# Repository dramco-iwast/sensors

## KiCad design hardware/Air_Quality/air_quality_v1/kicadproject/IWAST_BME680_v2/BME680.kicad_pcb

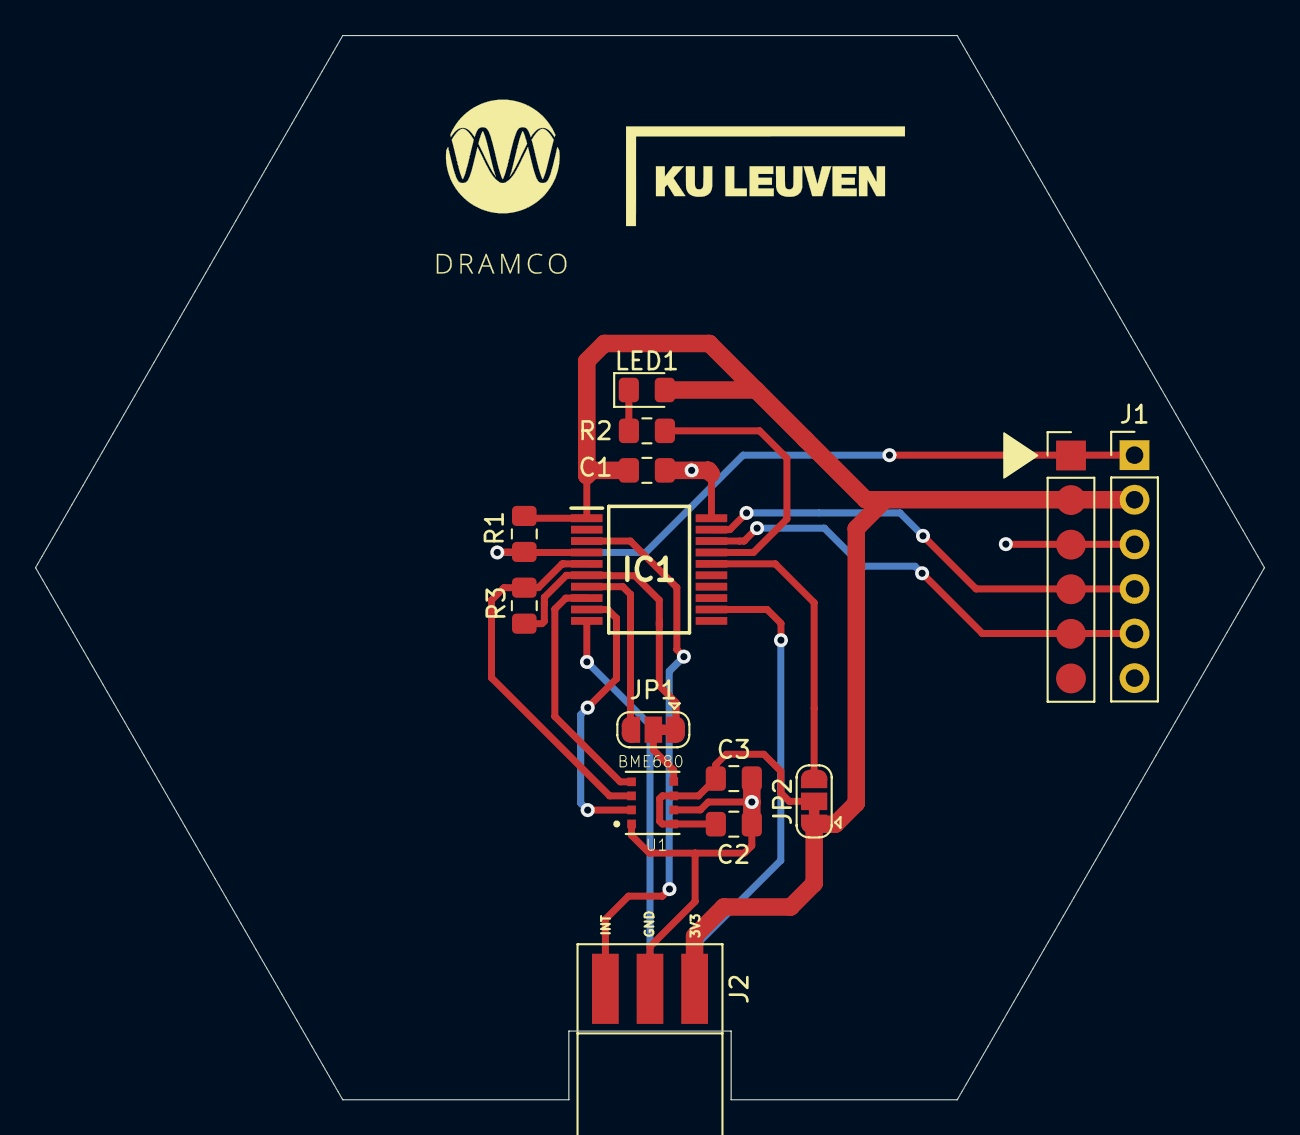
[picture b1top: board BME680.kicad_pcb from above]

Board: 2 copper layers, 70.0 x 60.6 mm, 13 parts (0 on the bottom side), 18 nets.

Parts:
C1, C2, C3: 100n; C_0805_2012Metric_Pad1.15x1.40mm_HandSolder
IC1: PIC16F18446-I_SS; SOP65P780X200-20N
J1: PICKit3; PinHeader_1x06_P2.54mm_Vertical
J2: MASTER; ConnectorHorizontalPcb
JP1: 3-wire; SolderJumper-3_P1.3mm_Bridged12_RoundedPad1.0x1.5mm
JP2: VDD Sensor; SolderJumper-3_P1.3mm_Bridged12_RoundedPad1.0x1.5mm
LED1: SML-D12Y1WT86; LED_0805_2012Metric_Pad1.15x1.40mm_HandSolder
R1, R3: 10k; R_0805_2012Metric_Pad1.15x1.40mm_HandSolder
R2: 1k; R_0805_2012Metric_Pad1.15x1.40mm_HandSolder
U1: BME680; PSON80P300X300X100-8N

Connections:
+3V3: C1.1, IC1.1, J1.2, J2.1, JP2.1, LED1.2, R1.1
/CS1: IC1.9, U1.2
/ICSPCLK: IC1.18, J1.5
/ICSPDAT: IC1.19, J1.4
/INT: IC1.3, J2.3
/MCLR: IC1.4, J1.1, R1.2
/MISO-SDI2: IC1.6, JP1.1, R3.2
/MOSI-SDO2: IC1.5, R3.1, U1.3
/NEWDATA: IC1.7, JP1.3
/SCK: IC1.8, U1.4
/SCL: IC1.10, J2.5
/SDA: IC1.12, J2.4
/USER_LED: IC1.17, R2.2
/VDD_sensor: IC1.16, JP2.3
GND: C1.2, C2.2, C3.2, IC1.20, J1.3, J2.2, U1.1, U1.7
unnamed: C2.1, C3.1, JP2.2, U1.6, U1.8
unnamed: JP1.2, U1.5
unnamed: LED1.1, R2.1

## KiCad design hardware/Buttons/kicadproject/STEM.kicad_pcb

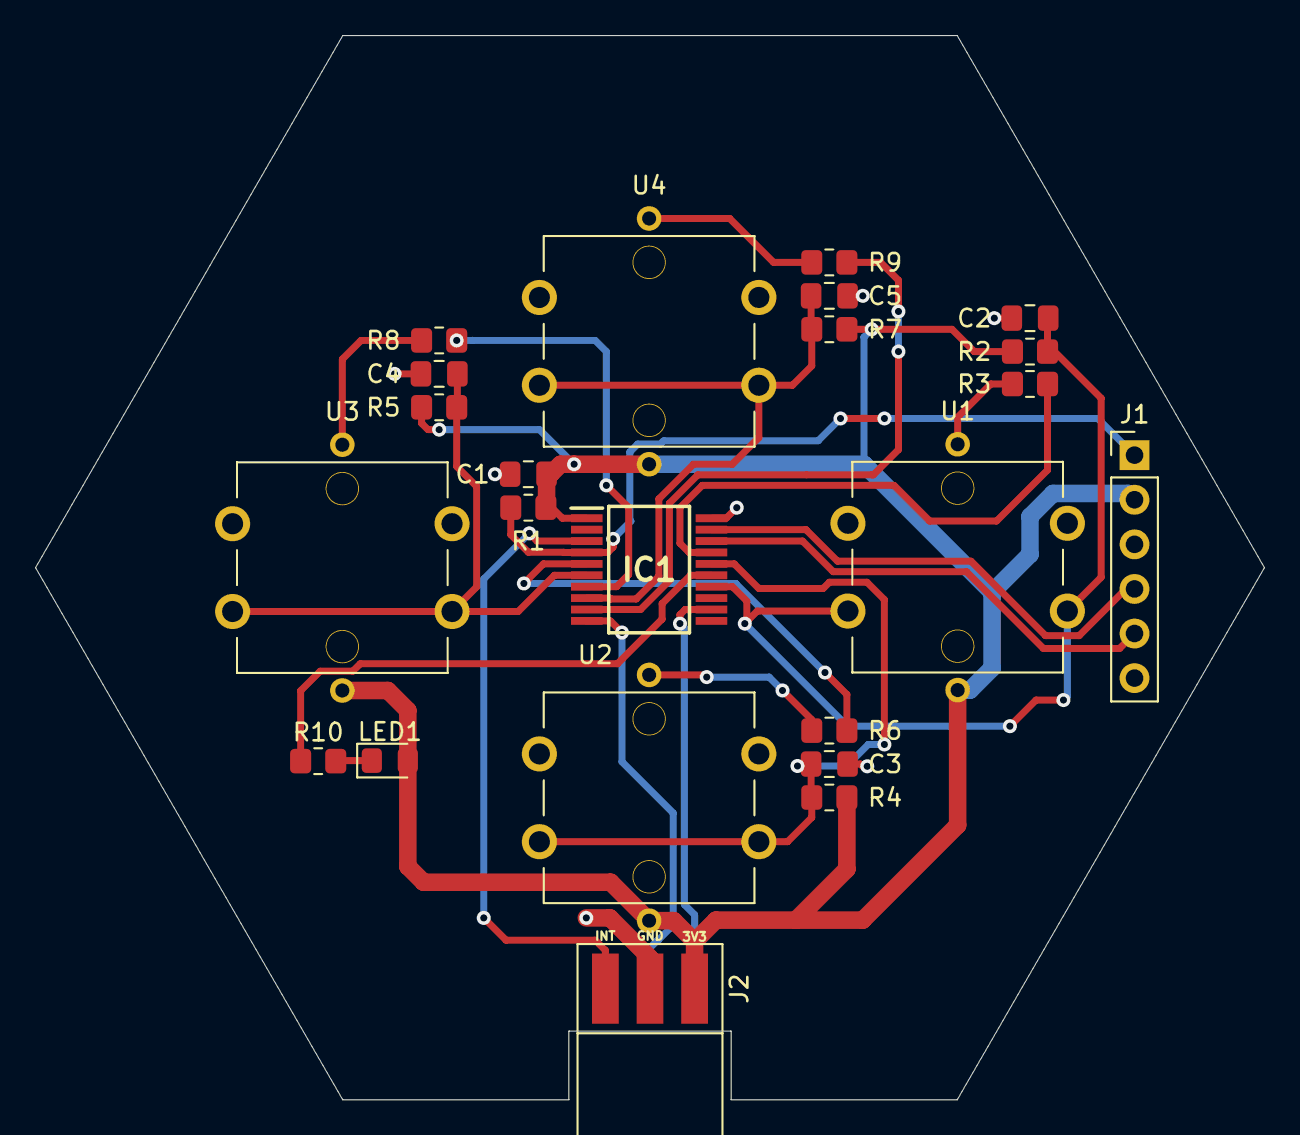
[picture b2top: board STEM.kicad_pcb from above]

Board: 2 copper layers, 70.0 x 60.6 mm, 23 parts (0 on the bottom side), 22 nets.

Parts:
C1, C2, C3, C4, C5: 100n; C_0805_2012Metric_Pad1.18x1.45mm_HandSolder
IC1: PIC16F18446-I_SS; SOP65P780X200-20N
J1: PICKit3; PinHeader_1x06_P2.54mm_Vertical
J2: MASTER; ConnectorHorizontalPcb
LED1: SML-D12Y1WT86; LED_0805_2012Metric_Pad1.15x1.40mm_HandSolder
R1: 10k; R_0805_2012Metric_Pad1.20x1.40mm_HandSolder
R2, R4, R5, R7: 100k; R_0805_2012Metric_Pad1.20x1.40mm_HandSolder
R3, R6, R8, R9, R10: 1k; R_0805_2012Metric_Pad1.20x1.40mm_HandSolder
U1, U2, U3, U4: button; aliButton

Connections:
+3V3: C1.1, IC1.1, J1.2, J2.1, LED1.2, R1.1, R2.1, R4.1, R5.1, R7.1, U1.5, U2.5, U3.5, U4.5
/ICSPCLK: IC1.18, J1.5
/ICSPDAT: IC1.19, J1.4
/INT: IC1.3, J2.3
/LSW1: IC1.17, R3.1
/LSW2: IC1.5, R6.1
/LSW3: IC1.7, R8.1
/LSW4: IC1.9, R9.1
/MCLR: IC1.4, J1.1, R1.2
/RC1: IC1.15, R10.1
/SCL: IC1.10, J2.5
/SDA: IC1.12, J2.4
/SW1: C2.2, IC1.14, R2.2, U1.1, U1.2
/SW2: C3.2, IC1.16, R4.2, U2.1, U2.2
/SW3: C4.2, IC1.6, R5.2, U3.1, U3.2
/SW4: C5.2, IC1.8, R7.2, U4.1, U4.2
GND: C1.2, C2.1, C3.1, C4.1, C5.1, IC1.20, J1.3, J2.2, U1.3, U1.4, U2.3, U2.4, U3.3, U3.4, U4.3, U4.4
unnamed: LED1.1, R10.2
unnamed: R3.2, U1.6
unnamed: R6.2, U2.6
unnamed: R8.2, U3.6
unnamed: R9.2, U4.6

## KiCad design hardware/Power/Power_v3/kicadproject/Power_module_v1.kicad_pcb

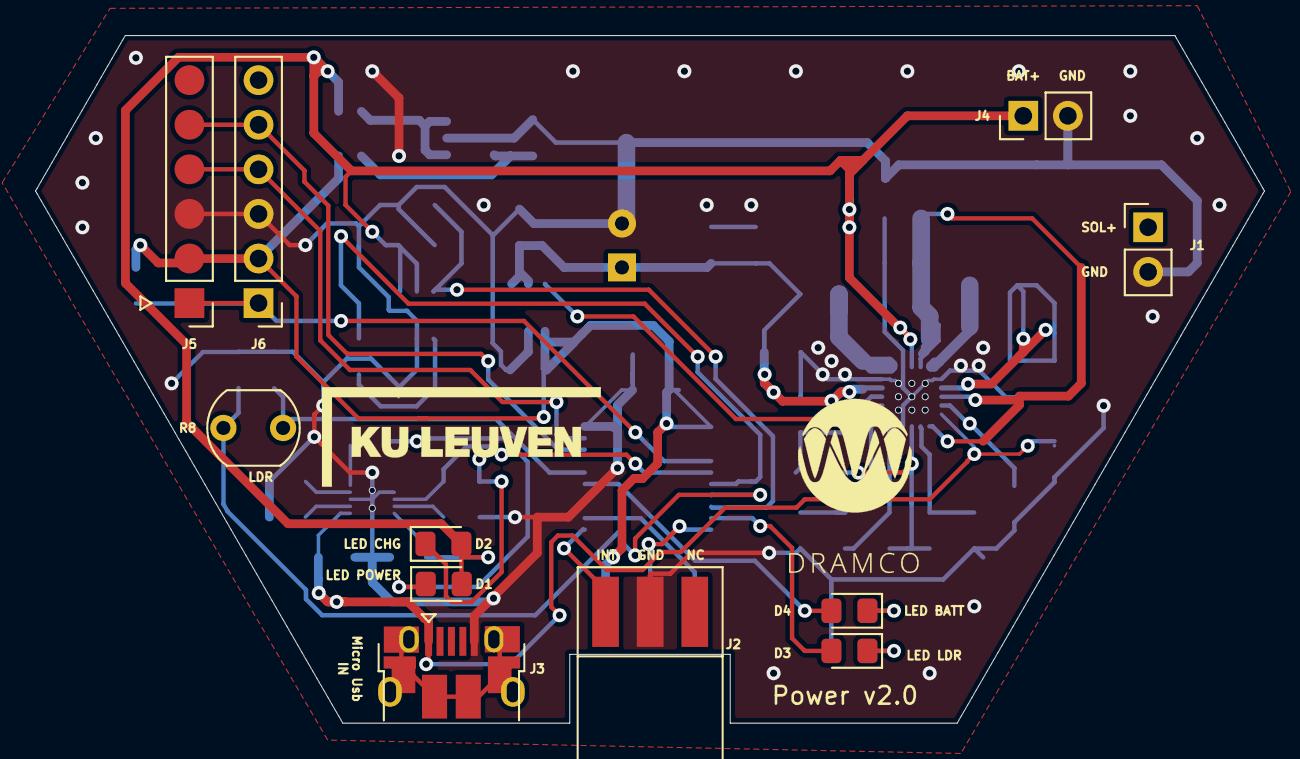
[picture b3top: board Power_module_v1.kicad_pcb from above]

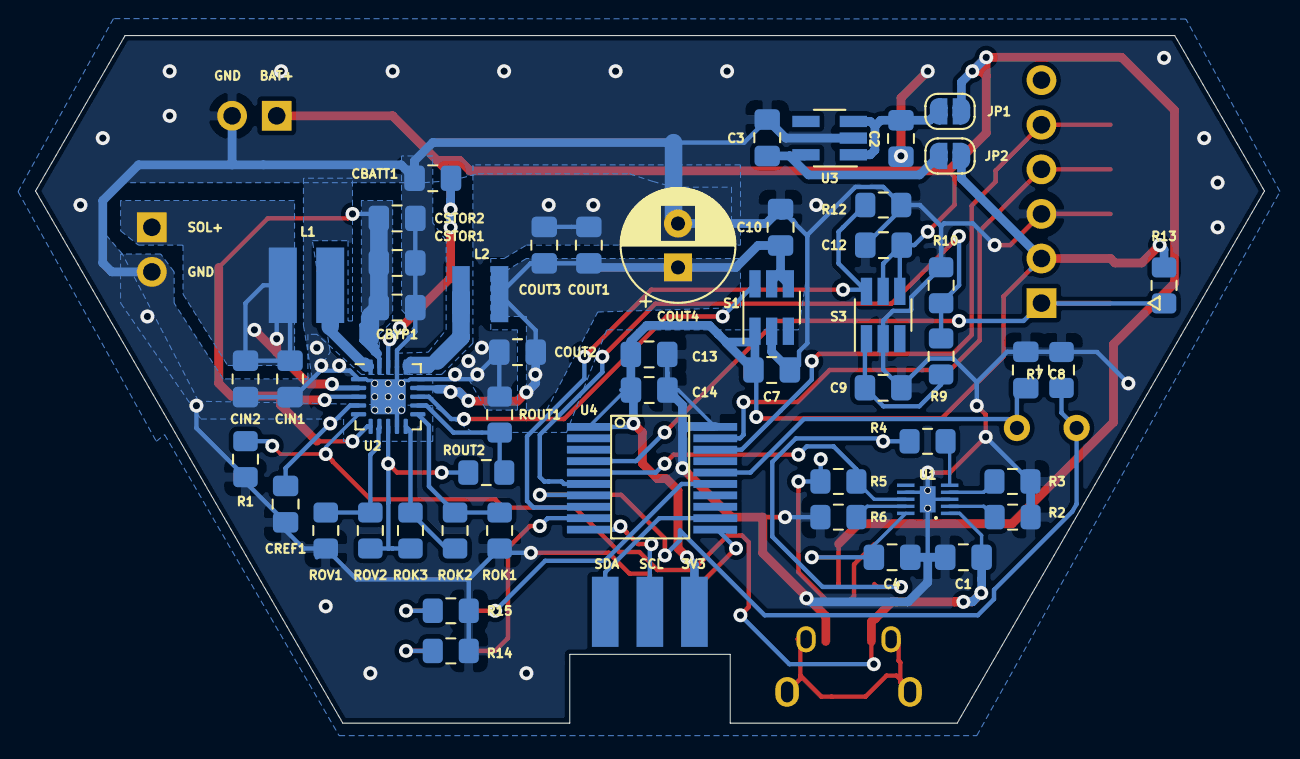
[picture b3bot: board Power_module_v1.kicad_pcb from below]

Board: 2 copper layers, 70.0 x 39.2 mm, 63 parts (52 on the bottom side), 40 nets.

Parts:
C1, C2, C3, C4, C7, C8, C9, C10, C12: 1 uF; C_0805_2012Metric_Pad1.18x1.45mm_HandSolder
C13: 10 uF; C_0805_2012Metric_Pad1.18x1.45mm_HandSolder
C14: 100 nF; C_0805_2012Metric_Pad1.18x1.45mm_HandSolder
CBATT1: DNP; C_0805_2012Metric_Pad1.18x1.45mm_HandSolder
CBYP1: 10 nF; C_0805_2012Metric_Pad1.18x1.45mm_HandSolder
CIN1: 4.7 uF; C_0805_2012Metric_Pad1.18x1.45mm_HandSolder
CIN2: 100n; C_0805_2012Metric_Pad1.18x1.45mm_HandSolder
COUT1: 100n; C_0805_2012Metric_Pad1.18x1.45mm_HandSolder
COUT2: 22 uF; C_0805_2012Metric_Pad1.18x1.45mm_HandSolder
COUT3: DNP; C_0805_2012Metric_Pad1.18x1.45mm_HandSolder
COUT4: 470 uF; CP_Radial_D6.3mm_P2.50mm
CREF1: 10 nF; C_0805_2012Metric_Pad1.18x1.45mm_HandSolder
CSTOR1: 4.7 uF; C_0805_2012Metric_Pad1.18x1.45mm_HandSolder
CSTOR2: DNP; C_0805_2012Metric_Pad1.18x1.45mm_HandSolder
D1, D2, D3, D4: LED; LED_0805_2012Metric_Pad1.15x1.40mm_HandSolder
J1: Conn_01x02; PinHeader_1x02_P2.54mm_Vertical
J2: Conn_02x03_motherboardconn; ConnectorHorizontalPcb
J3: USB_B_Micro; USB_Micro
J4: Conn_01x02_battery; PinHeader_1x02_P2.54mm_Vertical
J5, J6: Conn_01x06_programmer; PinHeader_1x06_P2.54mm_Vertical
JP1, JP2: SolderJumper_2_Open; SolderJumper-2_P1.3mm_Open_RoundedPad1.0x1.5mm
L1: 22 uH; Inductor_744031220_22uH
L2: 10 uH; Inductor_744029100_10uH
R1, R6, R9, R12, R13: 10k; R_0805_2012Metric_Pad1.15x1.40mm_HandSolder
R2: 1k; R_0805_2012Metric_Pad1.15x1.40mm_HandSolder
R3: 2k; R_0805_2012Metric_Pad1.15x1.40mm_HandSolder
R4, R5: 1.5k; R_0805_2012Metric_Pad1.15x1.40mm_HandSolder
R7: 27k; R_0805_2012Metric_Pad1.15x1.40mm_HandSolder
R8: LDR03; R_LDR_5.1x4.3mm_P3.4mm_Vertical
R10: 8.2k; R_0805_2012Metric_Pad1.15x1.40mm_HandSolder
R14, R15: 470; R_0805_2012Metric_Pad1.15x1.40mm_HandSolder
ROK1: 5.62M; R_0805_2012Metric_Pad1.15x1.40mm_HandSolder
ROK2: 5.49 M; R_0805_2012Metric_Pad1.15x1.40mm_HandSolder
ROK3: 1.9 M; R_0805_2012Metric_Pad1.15x1.40mm_HandSolder
ROUT1: 4.75 M; R_0805_2012Metric_Pad1.15x1.40mm_HandSolder
ROUT2: 8.25 M; R_0805_2012Metric_Pad1.15x1.40mm_HandSolder
ROV1: 5.61 M; R_0805_2012Metric_Pad1.15x1.40mm_HandSolder
ROV2: 7.32 M; R_0805_2012Metric_Pad1.15x1.40mm_HandSolder
S1, S3: TPS22860; SOT-23-6_Handsoldering
U1: BQ24040
U2: BQ25570; QFN-20-1EP_3.5x3.5mm_P0.5mm_EP2x2mm
U3: TPS705; SOT-23-5_HandSoldering
U4: PIC16F18446; PIC16F18446SSOP20PIN

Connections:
3V3: C7.1, C13.2, C14.2, J2.6, J5.2, J6.2, JP2.1, R13.1, S1.1, U4.1
3V3BUCK: C10.1, COUT1.1, COUT2.1, COUT3.1, COUT4.1, L2.1, S1.4, S1.5, U2.14
BAT+: C4.1, C12.1, CBATT1.1, D1.2, D2.2, J4.1, JP1.1, S3.4, S3.5, U1.10, U2.18
BAT_MEAS_EN: R12.1, S3.6, U4.8
BAT_VOLTAGE: R9.2, R10.1, U4.6
GND: C1.2, C2.2, C3.2, C4.2, C7.2, C8.2, C9.2, C10.2, C12.2, C13.1, C14.1, CBATT1.2, CBYP1.2, CIN1.2, CIN2.2, COUT1.2, COUT2.2, COUT3.2, COUT4.2, CREF1.2, CSTOR1.2, CSTOR2.2, J1.2, J2.2, J3.5, J4.2, J5.3, J6.3, R1.2, R2.2, R3.2, R6.2, R7.2, R10.2, R12.2, R14.2, R15.2, ROK1.2, ROUT1.2, ROV1.2, S1.2, S3.2, U1.3, U1.7, U1.11, U2.1, U2.9, U2.15, U2.17, U2.21, U3.2, U4.20
HYST: ROK2.1, ROK3.2, U2.10
ICSPCLK: J5.5, J6.5, U4.18
ICSPDAT: J5.4, J6.4, U4.19
INT: J2.3, U4.11
LDR: C8.1, R8.1, U4.16
LDR_VOLTAGE: R7.1, R8.2, U4.7
LED0: D3.2, U4.9
LED1: D4.2, U4.15
MCLR: J5.1, J6.1, R13.2, U4.4
unnamed: C2.1, JP1.2, U3.1, U3.3
unnamed: C3.1, JP2.2, U3.5
unnamed: C9.1, R9.1, S3.1
unnamed: CREF1.1, U2.4
unnamed: D1.1, R4.2
unnamed: D2.1, R5.2
unnamed: D3.1, R14.1
unnamed: D4.1, R15.1
unnamed: L1.1, U2.20
unnamed: L2.2, U2.16
unnamed: R2.1, U1.2
unnamed: R3.1, U1.4
unnamed: R4.1, U1.5
unnamed: R6.1, U1.9
unnamed: ROK3.1, ROUT2.1, ROV2.1, U2.8
unnamed: ROV1.1, ROV2.2, U2.7
PROG: ROK1.1, ROK2.2, U2.11
SCL: J2.5, U4.10
SDA: J2.4, U4.12
SET: ROUT1.1, ROUT2.2, U2.12
SOL+: CIN1.1, CIN2.1, J1.1, L1.2, U2.2
VBAT_OK_TO_MCU: S1.6, U2.13
VSTOR: CBYP1.1, CSTOR1.1, CSTOR2.1, U2.3, U2.6, U2.19
VUSB: C1.1, J3.1, R1.1, U1.1, U2.5
nCHG: R5.1, U1.8, U4.5

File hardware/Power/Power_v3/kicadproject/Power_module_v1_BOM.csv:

Id;Designator;Package;Quantity;Designation;Supplier and ref;;
1;C1,C2,C3,C4,C5,C6;C_0805_2012Metric_Pad1.15x1.40mm_HandSolder;6;1 uF;;;https://nl.mouser.com/ProductDetail/KEMET/C0805C105M8RACAUTO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
2;C7;C_0805_2012Metric_Pad1.15x1.40mm_HandSolder;1;10 uF;;;https://nl.mouser.com/ProductDetail/KEMET/C0805C106K9PACTU?q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
3;C8;C_0805_2012Metric_Pad1.15x1.40mm_HandSolder;1;100 nF;;;
4;CBYP1,CREF1;C_0805_2012Metric_Pad1.15x1.40mm_HandSolder;2;10 nF;;;https://nl.mouser.com/ProductDetail/Wurth-Elektronik/8850122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
5;CIN1,CSTOR1;C_0805_2012Metric_Pad1.15x1.40mm_HandSolder;2;4.7 uF;;;https://nl.mouser.com/ProductDetail/Walsin/0805X475M250CT?qs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
6;COUT1;C_0805_2012Metric_Pad1.15x1.40mm_HandSolder;1;22 uF;;;https://nl.mouser.com/ProductDetail/KEMET/C0805C226M9PACTU?q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
7;D1,D2,D3,D4;LED_0805_2012Metric_Pad1.15x1.40mm_HandSolder;4;LED;;;
8;J1;PinHeader_1x02_P2.54mm_Vertical;1;Conn_01x02;;;
9;J3;USB_Micro;1;USB_B_Micro;;;https://nl.mouser.com/ProductDetail/Amphenol-FCI/10118194-00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
10;J4;PinHeader_1x02_P2.54mm_Vertical;1;Conn_01x02_battery;;;
11;J5,J6;PinHeader_1x06_P2.54mm_Vertical;2;Conn_01x06_programmer;;;
12;JP1,JP2;SolderJumper-2_P1.3mm_Open_RoundedPad1.0x1.5mm;2;SolderJumper_2_Open;;;
13;L1;Inductor_744031220_22uH;1;22 uH;;;https://nl.mouser.com/ProductDetail/Wurth-Elektronik/7440312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
14;L2;Inductor_744029100_10uH;1;10 uH;;;https://nl.mouser.com/ProductDetail/Wurth-Elektronik/7440291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
15;R1,R6,R7,R8,R9,R10,R11;R_0805_2012Metric_Pad1.15x1.40mm_HandSolder;7;10k;;;
16;R2;R_0805_2012Metric_Pad1.15x1.40mm_HandSolder;1;1k;;;https://nl.mouser.com/ProductDetail/Vishay-Dale/CRCW08051K00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
17;R3;R_0805_2012Metric_Pad1.15x1.40mm_HandSolder;1;2k;;;https://nl.mouser.com/ProductDetail/Vishay-Dale/CRCW08052K00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
18;R4,R5;R_0805_2012Metric_Pad1.15x1.40mm_HandSolder;2;1.5k;;;
19;R12,R13;R_0805_2012Metric_Pad1.15x1.40mm_HandSolder;2;470;;;
20;ROK1;R_0805_2012Metric_Pad1.15x1.40mm_HandSolder;1;1.9 M;;;https://nl.mouser.com/ProductDetail/Vishay-Dale/CRCW08051M91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
21;ROK2;R_0805_2012Metric_Pad1.15x1.40mm_HandSolder;1;5.49 M;;;https://nl.mouser.com/ProductDetail/Vishay-Dale/CRCW08055M49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
22;ROK3;R_0805_2012Metric_Pad1.15x1.40mm_HandSolder;1;5.62M;;;https://nl.mouser.com/ProductDetail/Vishay-Dale/CRCW08055M62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
23;ROUT1;R_0805_2012Metric_Pad1.15x1.40mm_HandSolder;1;8.25 M;;;https://nl.mouser.com/ProductDetail/Vishay-Dale/CRCW08058M25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
24;ROUT2;R_0805_2012Metric_Pad1.15x1.40mm_HandSolder;1;4.75 M;;;https://nl.mouser.com/ProductDetail/Vishay-Dale/CRCW08054M75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
25;ROV1;R_0805_2012Metric_Pad1.15x1.40mm_HandSolder;1;7.32 M;;;https://nl.mouser.com/ProductDetail/Vishay-Dale/CRCW08057M32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
26;ROV2;R_0805_2012Metric_Pad1.15x1.40mm_HandSolder;1;5.61 M;;;https://nl.mouser.com/ProductDetail/Vishay-Dale/CRCW08055M60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
27;S1,S2;SOT-23-6_Handsoldering;2;TPS22860;;;https://nl.mouser.com/ProductDetail/Texas-Instruments/TPS228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
28;U1;BQ24040;1;BQ24040;;;https://nl.mouser.com/ProductDetail/Texas-Instruments/BQ2404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
29;U2;QFN-20-1EP_3.5x3.5mm_P0.5mm_EP2x2mm;1;BQ25570;;;https://nl.mouser.com/ProductDetail/Texas-Instruments/BQ2557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
30;U3;SOT-23-5_HandSoldering;1;TPS705;;;https://nl.mouser.com/ProductDetail/Texas-Instruments/TPS7A0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
31;U4;PIC16F18446SSOP20PIN;1;PIC16F18446;;;https://nl.mouser.com/ProductDetail/Microchip-Technology/PIC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
32;J2;ConnectorHorizontalPcb;1;Conn_02x03_motherboardconn;;;https://nl.mouser.com/ProductDetail/Harwin/M20-9980345?qs=%2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

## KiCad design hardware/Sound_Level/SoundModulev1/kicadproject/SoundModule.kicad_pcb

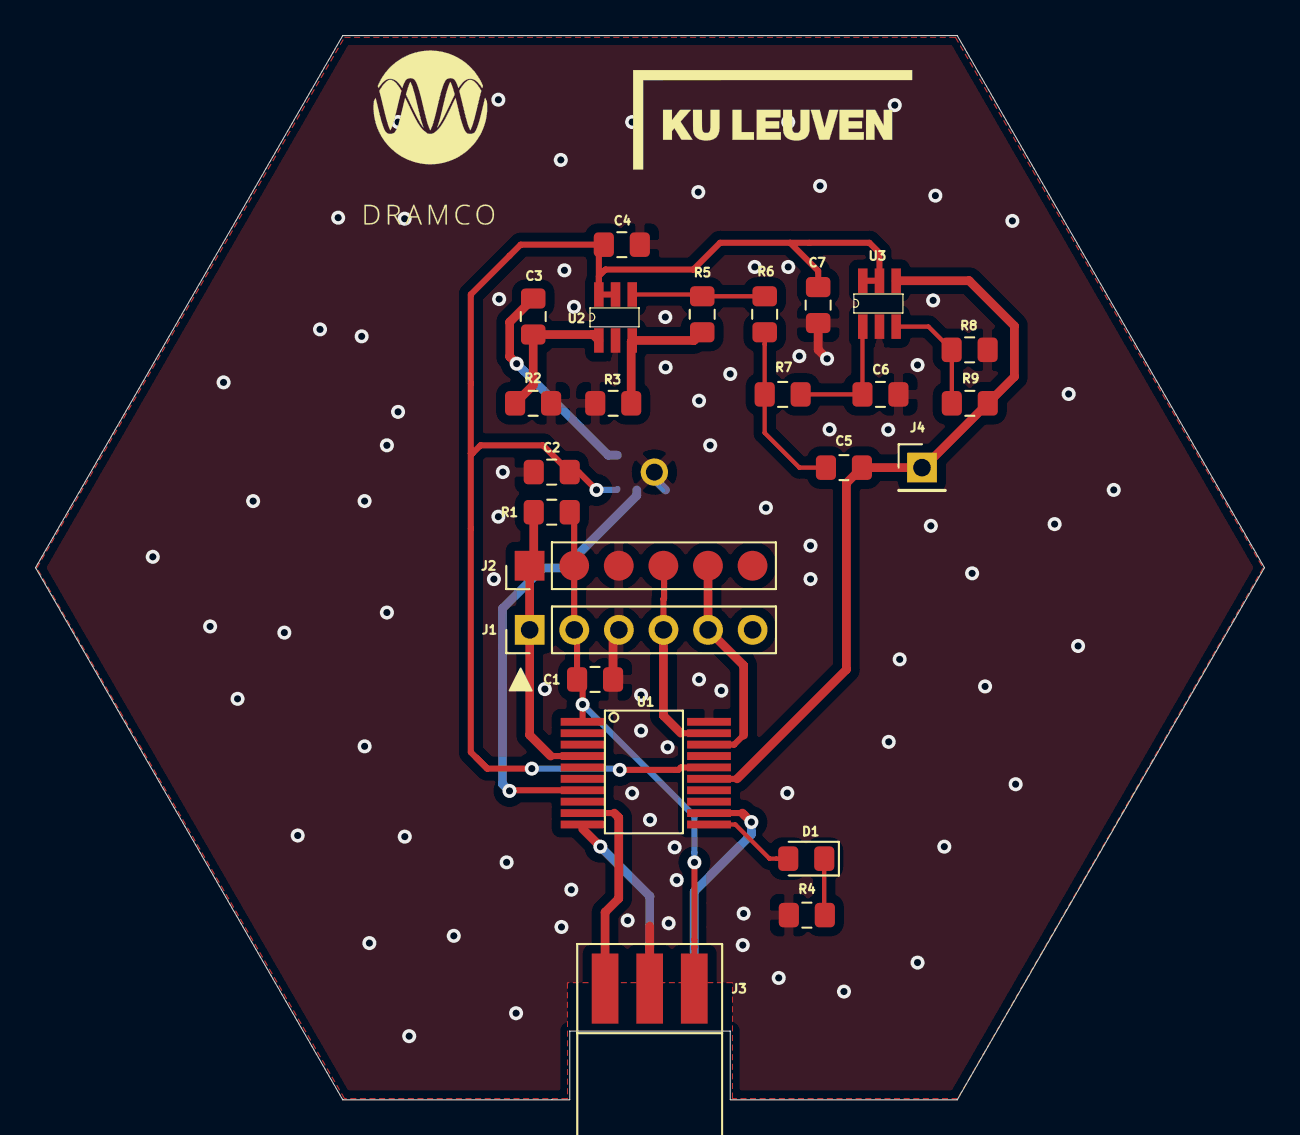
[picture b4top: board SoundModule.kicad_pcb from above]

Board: 2 copper layers, 70.0 x 60.6 mm, 25 parts (1 on the bottom side), 20 nets.

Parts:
C1, C2, C4, C7: 100 nF; C_0805_2012Metric_Pad1.15x1.40mm_HandSolder
C3: 47 nF; C_0805_2012Metric_Pad1.15x1.40mm_HandSolder
C5, C6: 2.2 nF; C_0805_2012Metric_Pad1.15x1.40mm_HandSolder
D1: LED; LED_0805_2012Metric_Pad1.15x1.40mm_HandSolder
J1, J2: ProgramPic; PinHeader_1x06_P2.54mm_Vertical
J3: Conn_02x03_Top_Bottom; ConnectorHorizontalPcb
J4: VanalogTestPin; PinHeader_1x01_P2.54mm_Vertical
MK1: VesperVM1010; VESPER_VM1010
R1, R6, R7: 10k; R_0805_2012Metric_Pad1.15x1.40mm_HandSolder
R2: 120k; R_0805_2012Metric_Pad1.15x1.40mm_HandSolder
R3: 18k; R_0805_2012Metric_Pad1.15x1.40mm_HandSolder
R4: 470; R_0805_2012Metric_Pad1.15x1.40mm_HandSolder
R5: 560k; R_0805_2012Metric_Pad1.15x1.40mm_HandSolder
R8: 2.7k; R_0805_2012Metric_Pad1.15x1.40mm_HandSolder
R9: 1k; R_0805_2012Metric_Pad1.15x1.40mm_HandSolder
U1: PIC16F18446; PIC16F18446SSOP20PIN
U2, U3: TLV341A; TLV341 SOT-23-6

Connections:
3V3: C1.1, J1.2, J2.2, J3.1, R1.1, U1.1
GND: C1.2, C2.2, C4.2, C6.2, C7.2, J1.3, J2.3, J3.2, MK1.4, MK1.8, R2.2, R3.1, R4.2, R8.2, U1.20, U2.2, U3.2
ICSPCLK: J1.5, J2.5, U1.18
ICSPDAT: J1.4, J2.4, U1.19
INT: J3.3, U1.9
LEDdebug: D1.2, U1.11
MCLR: J1.1, J2.1, R1.2, U1.4
unnamed: C3.1, R2.1, U2.1
unnamed: C3.2, MK1.1
unnamed: C5.2, R6.1, R7.2
unnamed: C6.1, R7.1, U3.1
unnamed: D1.1, R4.1
unnamed: R3.2, R5.2, U2.3
unnamed: R5.1, R6.2, U2.4
unnamed: R8.1, R9.2, U3.3
SCL: J3.5, U1.10
SDA: J3.4, U1.12
VDDsensor: C2.1, C4.1, C7.1, MK1.6, U1.16, U2.5, U2.6, U3.5, U3.6
Vanalog: C5.1, J4.1, R9.1, U1.15, U3.4
mode: MK1.5, U1.7

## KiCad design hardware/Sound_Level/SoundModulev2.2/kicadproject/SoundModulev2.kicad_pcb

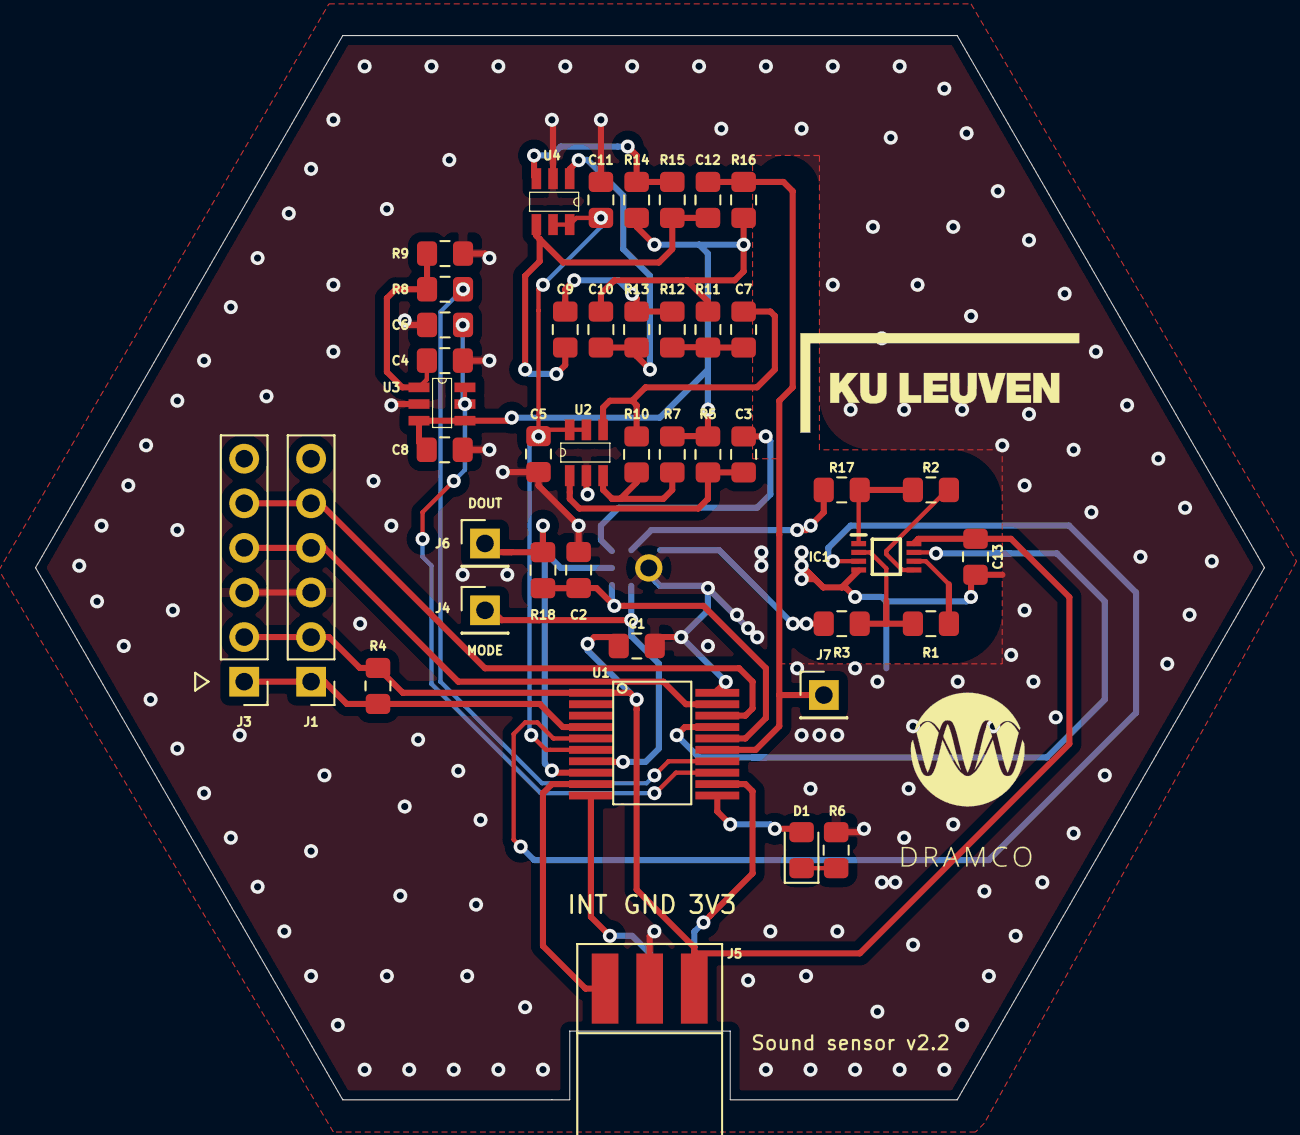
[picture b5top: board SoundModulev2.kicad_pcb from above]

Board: 2 copper layers, 70.0 x 60.6 mm, 44 parts (1 on the bottom side), 36 nets.

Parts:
C1, C2, C5, C6, C11, C13: 100 nF; C_0805_2012Metric_Pad1.15x1.40mm_HandSolder
C3, C7, C12: 47n; C_0805_2012Metric_Pad1.15x1.40mm_HandSolder
C4, C8: 10 uF; C_0805_2012Metric_Pad1.15x1.40mm_HandSolder
C9, C10: 2.2 nF; C_0805_2012Metric_Pad1.15x1.40mm_HandSolder
D1: LED; LED_0805_2012Metric_Pad1.15x1.40mm_HandSolder
IC1: TS5A2066DCUR; SOP50P310X90-8N
J1, J3: ProgramPic; PinHeader_1x06_P2.54mm_Vertical
J4, J6: Conn_01x01; PinHeader_1x01_P2.54mm_Vertical
J5: Conn_02x03_Top_Bottom; ConnectorHorizontalPcb
J7: VanalogTestPin; PinHeader_1x01_P2.54mm_Vertical
MIC: VesperVM1010; VESPER_VM1010
R1, R2: 36k; R_0805_2012Metric_Pad1.15x1.40mm_HandSolder
R3, R17: 9k; R_0805_2012Metric_Pad1.15x1.40mm_HandSolder
R4, R12, R13: 10k; R_0805_2012Metric_Pad1.15x1.40mm_HandSolder
R5, R11, R16: 120k; R_0805_2012Metric_Pad1.15x1.40mm_HandSolder
R6: 470; R_0805_2012Metric_Pad1.15x1.40mm_HandSolder
R7: 18k; R_0805_2012Metric_Pad1.15x1.40mm_HandSolder
R8, R9: 100k; R_0805_2012Metric_Pad1.15x1.40mm_HandSolder
R10: 560k; R_0805_2012Metric_Pad1.15x1.40mm_HandSolder
R14: 2.7k; R_0805_2012Metric_Pad1.15x1.40mm_HandSolder
R15: 1k; R_0805_2012Metric_Pad1.15x1.40mm_HandSolder
R18: 500k; R_0805_2012Metric_Pad1.15x1.40mm_HandSolder
U1: PIC16F18446; PIC16F18446SSOP20PIN
U2, U3, U4: TLV341A; TLV341 SOT-23-6

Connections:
3V3: C1.1, C13.1, IC1.8, J1.2, J3.2, J5.1, R4.1, U1.1
GA1: MIC.3, R3.2
GA2: MIC.2, R17.2
GND: C1.2, C2.2, C4.2, C5.2, C6.1, C8.2, C11.2, C13.2, IC1.4, J1.3, J3.3, J5.2, MIC.4, MIC.8, R6.2, R9.2, U1.20, U2.2, U3.2, U4.2
ICSPCLK: J1.5, J3.5, U1.18
ICSPDAT: J1.4, J3.4, U1.19
INT: J5.3, U1.9
LEDdebug: D1.2, U1.11
MCLR: J1.1, J3.1, R4.2, U1.4
unnamed: C3.1, R5.1, U2.1
unnamed: C3.2, MIC.1
unnamed: C4.1, R8.2, R9.1, U3.1
unnamed: C7.1, R11.1, R12.2
unnamed: C7.2, R10.1, U2.4
unnamed: C9.2, R12.1, R13.2
unnamed: C10.1, R13.1, U4.1
unnamed: C9.1, C12.2, R15.1, U4.4
unnamed: D1.1, R6.1
unnamed: IC1.1, R2.2, R17.1
unnamed: IC1.2, R1.2, R3.1
unnamed: IC1.5, R2.1
unnamed: IC1.6, R1.1
unnamed: R7.2, R10.2, U2.3
unnamed: R14.1, R15.2, U4.3
SCL: J5.5, U1.10
SDA: J5.4, U1.12
THRESHOLD1: IC1.7, U1.17
THRESHOLD2: IC1.3, U1.5
VDDAMP: C5.1, C11.1, U1.6, U2.5, U2.6, U4.5, U4.6
VDDBIAS: R8.1, U1.14
VDDBIASAMP: C6.2, U1.13, U3.5, U3.6
VDDsensor: C2.1, MIC.6, R18.1, U1.16
Vanalog: C12.1, J7.1, R16.1, U1.15
biasvoltage: C8.1, C10.2, R5.2, R7.1, R11.2, R14.2, R16.2, U3.3, U3.4
dout: J6.1, MIC.7, R18.2, U1.8
mode: J4.1, MIC.5, U1.7

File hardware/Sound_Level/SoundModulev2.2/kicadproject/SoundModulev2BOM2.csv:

Id;Designator;Behuizing;Hoeveelheid;Orientatie;Leverancier en ref
;;;;;
;;;;;
;;;;;
4;R18;R_0805_2012Metric_Pad1.15x1.40mm_HandSolder;1;500k;
5;IC1;SOP50P310X90-8N;1;TS5A2066DCUR;
6;R17,R3;R_0805_2012Metric_Pad1.15x1.40mm_HandSolder;2;9k;
7;R2,R1;R_0805_2012Metric_Pad1.15x1.40mm_HandSolder;2;36k;
8;C13,C1,C2,C5,C6,C11;C_0805_2012Metric_Pad1.15x1.40mm_HandSolder;6;100 nF;
;;;;;
10;C3,C7,C12;C_0805_2012Metric_Pad1.15x1.40mm_HandSolder;3;47n;
11;C9,C10;C_0805_2012Metric_Pad1.15x1.40mm_HandSolder;2;2.2 nF;
12;D1;LED_0805_2012Metric_Pad1.15x1.40mm_HandSolder;1;LED;
13;J1,J3;PinHeader_1x06_P2.54mm_Vertical;2;ProgramPic;
14;J7;PinHeader_1x01_P2.54mm_Vertical;1;VanalogTestPin;
15;MK1;VESPER_VM1010;1;VesperVM1010;
16;R4,R12,R13;R_0805_2012Metric_Pad1.15x1.40mm_HandSolder;3;10k;
17;R6;R_0805_2012Metric_Pad1.15x1.40mm_HandSolder;1;470;
18;R5,R11,R16;R_0805_2012Metric_Pad1.15x1.40mm_HandSolder;3;120k;
19;R7;R_0805_2012Metric_Pad1.15x1.40mm_HandSolder;1;18k;
20;R8,R9;R_0805_2012Metric_Pad1.15x1.40mm_HandSolder;2;100k;
21;R10;R_0805_2012Metric_Pad1.15x1.40mm_HandSolder;1;560k;
22;R14;R_0805_2012Metric_Pad1.15x1.40mm_HandSolder;1;2.7k;
23;R15;R_0805_2012Metric_Pad1.15x1.40mm_HandSolder;1;1k;
24;U1;PIC16F18446SSOP20PIN;1;PIC16F18446;
25;U2,U3,U4;TLV341 SOT-23-6;3;TLV341A;OK
26;C4,C8;C_0805_2012Metric_Pad1.15x1.40mm_HandSolder;2;10 uF;
